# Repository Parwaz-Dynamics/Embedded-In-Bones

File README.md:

# Embedded-In-Bones 🦴

**My personal journey into embedded systems, from bare-metal programming to real-time operating systems.**

This repository documents my hands-on learning journey in embedded systems. It contains experiments, exercises, and projects as I work toward understanding what happens inside a microcontroller — from executing individual instructions to building real-time, event-driven applications.

## 🎯 Why This Repository?

I've worked with Arduino, ESP32, and Teensy platforms, along with STM32 microcontrollers such as the STM32F103, STM32F411, and STM32H723. Although I had some practical experience, I realized there was still a lot I wanted to understand at a deeper level.

Instead of relying entirely on frameworks and libraries, I decided to go back to the fundamentals: learning how processors execute instructions, how memory works, how interrupts are handled, and how embedded software can be designed to operate reliably in real time.

This repository is a record of that journey — including the concepts I've learned, the challenges I've faced, and the things I still need to explore.

## 📂 Learning Journey

### 1. Bare-Metal STM32F446

**Learning resource:** *Embedded Systems with ARM Cortex-M Microcontrollers in Assembly Language and C* by Dr. Yifeng Zhu.

I started by learning how to program a microcontroller close to the hardware, using ARM assembly language and C.

Topics covered include:

- ARM Cortex-M instruction set and processor registers
- Arithmetic, logical, shifting, and branching instructions
- Subroutines, structured programming, and mixing assembly with C
- Stack and heap fundamentals
- Static and volatile variables
- GPIO configuration and digital I/O
- Interrupts and timers
- Basic communication protocols
- Memory organization, including Flash and RAM
- Debugging and the software build process

This book helped me develop a clearer understanding of what happens inside a microcontroller when a program runs, rather than treating the hardware as a black box.

Along the way, I also gained practical experience with **Keil µVision**, ARM Compiler 6, and the GNU toolchain. I explored debugging, ELF files, linker scripts, and how code and data are organized in memory.

The final DSP chapter is still on my list to revisit.

📁 **Folder:** `Bare-Metal STM32F446/`

### 2. Real-Time Operating Systems — Quantum Leaps

**Learning resource:** [Quantum Leaps — YouTube lectures](https://www.youtube.com/@StateMachineCOM)

After completing most of the bare-metal material, I wanted to understand how embedded applications manage multiple concurrent activities and respond to events in real time.

I started following the Modern Embedded Systems programming lectures by Quantum Leaps. The early material reinforced some concepts I had already studied, but things became more challenging as the lectures progressed into interrupt handling, concurrency, and real-time operating systems.

During this stage, I worked through **MiROS**, a small real-time operating system, and then moved on to **QPC (QP/C)**.

Building and studying MiROS helped me explore concepts such as:

- Tasks and cooperative scheduling
- Preemptive scheduling and context switching
- Interrupt handling and synchronization
- Semaphores and blocking
- Communication and synchronization between concurrent tasks

My journey with QPC is ongoing. Next, I plan to explore state machines and event-driven programming to better understand how embedded applications can be structured without relying entirely on traditional blocking task-based designs.

📁 **Folder:** `Quantum Leap/`

## 🛠️ Tools & Technologies

- **Microcontrollers:** STM32F446 and other STM32 platforms
- **Programming languages:** C and ARM Assembly
- **IDE:** Keil µVision
- **Toolchains:** ARM Compiler 6 and GNU toolchain
- **Core topics:** Bare-metal programming, interrupts, timers, memory management, debugging, and RTOS fundamentals
- **RTOS / frameworks:** MiROS and QP/C

## 🚧 What's Next?

This journey is far from over.

This list will evolve as I learn and discover new areas worth exploring.

## 📌 A Note to Myself

Keep it up

------------------------------------------------

## 🔄 A Change in Direction: PCB Design & Embedded Systems Engineering

For now, I'm taking a slight detour from RTOS development to explore another important side of embedded systems: **PCB design and hardware development**.

I want to move beyond working with development boards and start understanding how to design and build my own PCBs. My plan is to learn the fundamentals of PCB design and manufacture one or two boards of my own.

Alongside this, I'll be reading *Making Embedded Systems* by **Elecia White**. I see this book as an opportunity to learn more about the broader engineering side of embedded systems, including how embedded projects are designed, developed, debugged, and managed.

My current plan is to:

- Learn the fundamentals of PCB design.
- Design and build one or two PCBs to gain practical experience.
- Read *Making Embedded Systems* by Elecia White.
- Return to Miro Samek's Modern Embedded Systems lectures after establishing a basic understanding of PCB design and completing my first boards.
- Meanwhile work on another project where I can practice the already learned techniques.

I'll resume the lectures from **Lecture #29 — Object-Oriented Programming**, where I paused.

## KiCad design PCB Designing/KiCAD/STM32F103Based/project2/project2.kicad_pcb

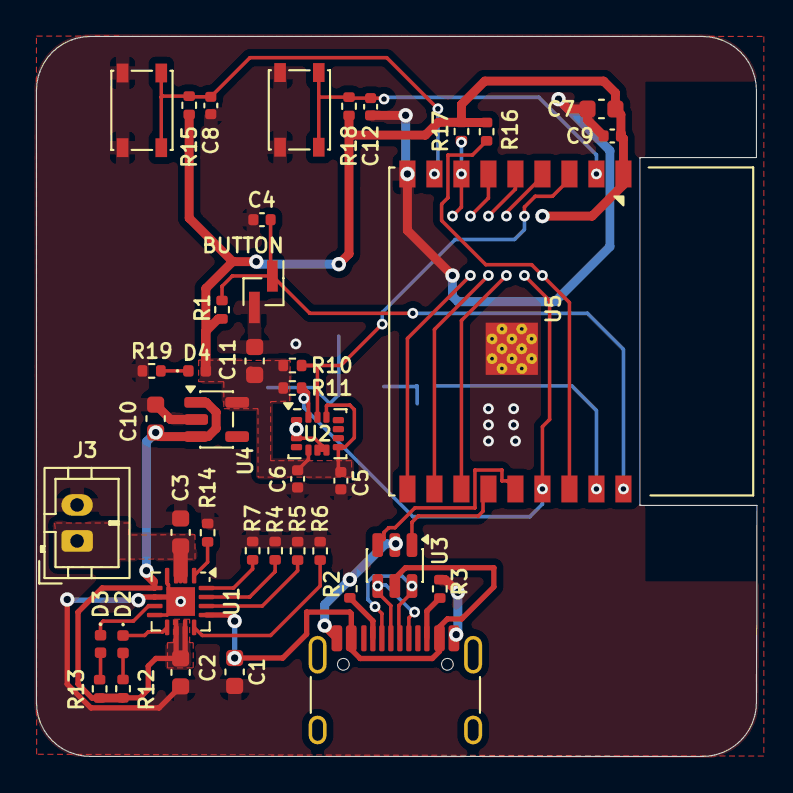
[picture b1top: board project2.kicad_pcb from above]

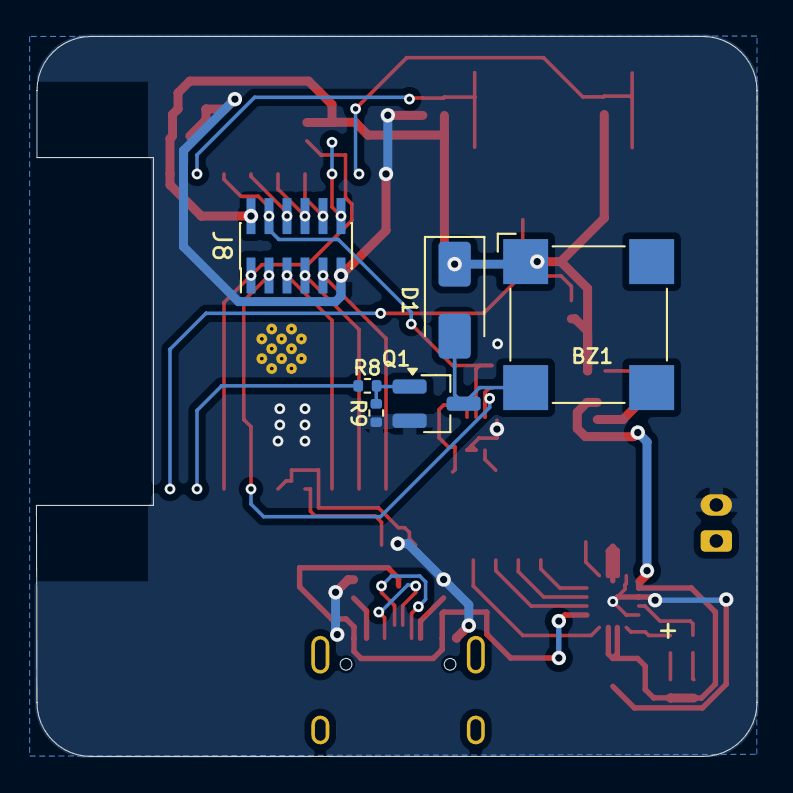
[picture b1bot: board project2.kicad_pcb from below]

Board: 2 copper layers, 40.0 x 40.0 mm, 48 parts (6 on the bottom side), 37 nets.

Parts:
BZ1: Buzzer; MagneticBuzzer_CUI_CMT-8504-100-SMT
C1, C10, C11: 1u; C_0603_1608Metric
C2, C3: 4u7; C_0603_1608Metric
C4, C5, C6, C8, C9, C12: 100n; C_0402_1005Metric
C7: 10u; C_0603_1608Metric
D1: SS14; D_SMA
D2, D3, D4: LED; LED_0402_1005Metric
J1: TYPE_C_31_M_12; USB_C_Receptacle_HRO_TYPE-C-31-M-12
J2: PLAY_BUTTON; PinHeader_1x02_P1.00mm_Vertical_SMD_Pin1Left
J3: BATT; JST_PH_B2B-PH-K_1x02_P2.00mm_Vertical
J8: Conn_02x06_Counter_Clockwise; PinHeader_2x06_P1.00mm_Vertical_SMD
Q1: AO3400A; SOT-23_Handsoldering
R1, R2, R3, R10, R11, R15, R18: 5k1; R_0402_1005Metric
R4: 4k7; R_0402_1005Metric
R5: 72k; R_0402_1005Metric
R6: 1k2; R_0402_1005Metric
R7: 3k3; R_0402_1005Metric
R8: 100; R_0402_1005Metric
R9, R14, R16, R17: 10k; R_0402_1005Metric
R12, R13, R19: 1k; R_0402_1005Metric
SW1: BOOT; SW_SPST_PTS810
SW2: NRST; SW_SPST_PTS810
U1: BQ24074RGT; VQFN-16-1EP_3x3mm_P0.5mm_EP1.6x1.6mm
U2: LSM6DS3TR-C; LGA-14_3x2.5mm_P0.5mm_LayoutBorder3x4y
U3: USBLC6-2SC6; SOT-23-6
U4: AP2112K-3.3; SOT-23-5
U5: ESP32-C3-WROOM-02

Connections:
+3.3V: BZ1.1 (+), C5.2, C6.2, C7.1, C9.1, C11.1, D1.1 (K), D4.2 (A), J8.2, R1.2, R10.2, R11.2, R15.2, R16.2, R17.2, R18.2, U2.5 (VDDIO), U2.8 (VDD), U2.12 (CS), U4.5 (VOUT), U5.1 (3V3)
+BATT: C3.1, J3.1, U1.2 (BAT), U1.3 (BAT)
/BOOT: C8.1, R15.1, SW1.2, U5.8 (IO9)
/BUZZER_MCU: R8.2, U5.17 (IO1)
/CHIP_EN: C12.1, R18.1, SW2.2, U5.2 (EN)
/I2C_SCL: J8.4, R10.1, U2.13 (SCL), U5.3 (IO4)
/I2C_SDA: J8.3, R11.1, U2.14 (SDA), U5.15 (IO3)
/IO2: J8.1, R16.1, U5.16 (IO2)
/IO5: J8.6, U5.4 (IO5)
/IO6: J8.8, U5.5 (IO6)
/IO7: J8.10, U5.6 (IO7)
/IO8: J8.12, R17.1, U5.7 (IO8)
/IO10: J8.9, U5.10 (IO10)
/MCU_USB_D_N: U3.1 (I/O1), U5.13 (IO18)
/MCU_USB_D_P: U3.3 (I/O2), U5.14 (IO19)
/PLAY_BUTTON_MCU: C4.1, J2.1, R1.1, U5.18 (IO0)
/PWR_LED_K: D4.1 (K), R19.1
/RXD: J8.7, U5.11 (IO20/RXD)
/TXD: J8.5, U5.12 (IO21/TXD)
/USB_D_N: J1.A7 (D-), J1.B7 (D-), U3.6 (I/O1)
/USB_D_P: J1.A6 (D+), J1.B6 (D+), U3.4 (I/O2)
GND: C1.2, C2.2, C3.2, C4.2, C5.1, C6.1, C7.2, C8.2, C9.2, C10.2, C11.2, C12.2, J1.A1 (GND), J1.A12 (GND), J1.B1 (GND), J1.B12 (GND), J2.2, J3.2, J8.11, Q1.2 (S), R2.2, R3.2, R4.1, R5.1, R6.1, R7.1, R9.2, R14.2, R19.2, SW1.1, SW2.1, U1.4 (~CE), U1.6 (EN1), U1.8 (VSS), U1.17 (VSS), U2.1 (SDO/SA0), U2.2 (SDX), U2.3 (SCX), U2.6 (GND), U2.7 (GND), U3.2 (GND), U4.2 (GND), U5.9 (GND), U5.19 (GND)
unnamed: BZ1.2 (-), D1.2 (A), Q1.3 (D)
unnamed: D2.2 (A), R12.1
unnamed: D2.1 (K), U1.9 (~CHG)
unnamed: D3.2 (A), R13.1
unnamed: D3.1 (K), U1.7 (~PGOOD)
unnamed: J1.A5 (CC1), R2.1
unnamed: J1.B5 (CC2), R3.1
unnamed: Q1.1 (G), R8.1, R9.1
unnamed: R6.2, U1.12 (ILIM)
unnamed: R7.2, U1.16 (ISET)
unnamed: R4.2, U1.15 (ITERM)
unnamed: R5.2, U1.14 (TMR)
unnamed: R14.1, U1.1 (TS)
VBUS: C1.1, J1.A4 (VBUS), J1.A9 (VBUS), J1.B4 (VBUS), J1.B9 (VBUS), U1.13 (IN), U3.5 (VBUS)
VSYS: C2.1, C10.1, R12.2, R13.2, U1.5 (EN2), U1.10 (OUT), U1.11 (OUT), U4.1 (VIN), U4.3 (EN)

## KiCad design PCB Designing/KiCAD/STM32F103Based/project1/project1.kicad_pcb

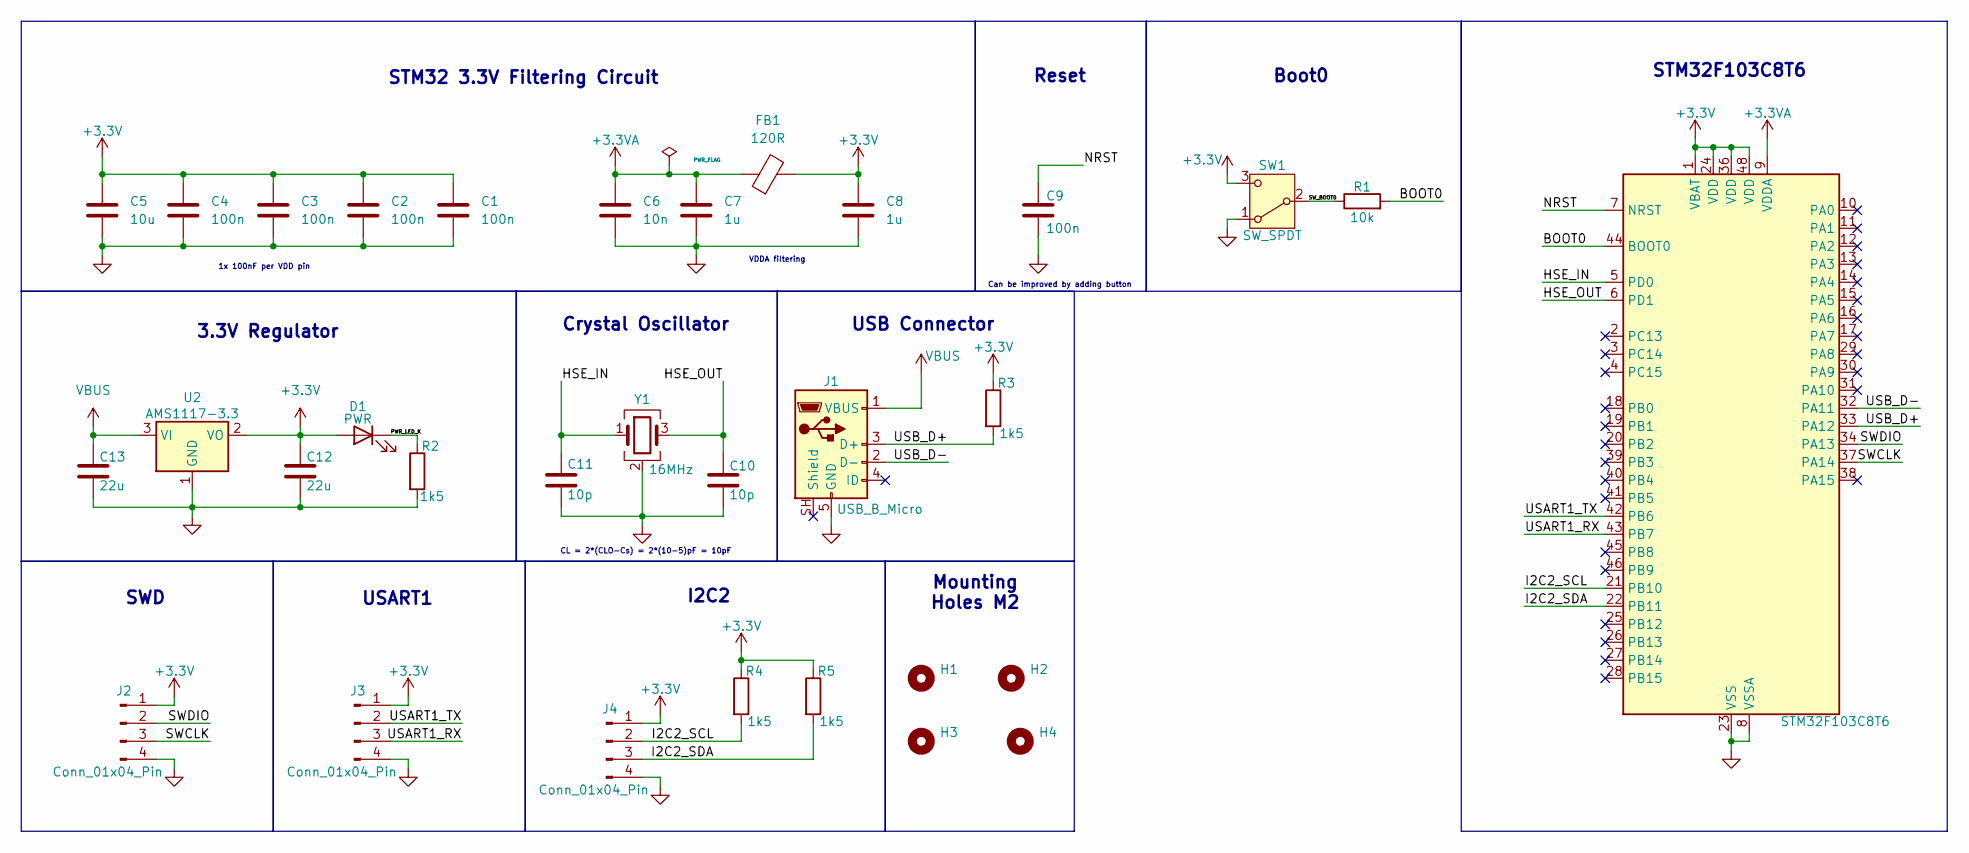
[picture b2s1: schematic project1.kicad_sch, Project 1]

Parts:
C1, C2, C3, C4, C9: 100n; C_0402_1005Metric
C5: 10u; C_0603_1608Metric
C6: 10n; C_0402_1005Metric
C7, C8: 1u; C_0402_1005Metric
C10, C11: 10p; C_0402_1005Metric
C12, C13: 22u; C_0805_2012Metric
D1: PWR; LED_0603_1608Metric
FB1: 120R; L_0603_1608Metric
H1, H2, H3, H4: MountingHole; MountingHole_2.2mm_M2
J1: USB_B_Micro; USB_Micro-B_Wuerth_629105150521
J2, J3, J4: Conn_01x04_Pin; PinHeader_1x04_P2.54mm_Vertical
R1: 10k; R_0402_1005Metric
R2, R3, R4, R5: 1k5; R_0402_1005Metric
SW1: SW_SPDT; SW_SPDT_PCM12
U1: STM32F103C8T6; LQFP-48_7x7mm_P0.5mm
U2: AMS1117-3.3; SOT-223-3_TabPin2
Y1: 16MHz; Crystal_SMD_3225-4Pin_3.2x2.5mm

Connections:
+3.3V: C1.1, C2.1, C3.1, C4.1, C5.1, C8.1, C12.1, D1.2 (A), FB1.2, J2.1, J3.1, J4.1, R3.1, R4.1, R5.1, SW1.3 (C), U1.1 (VBAT), U1.24 (VDD), U1.36 (VDD), U1.48 (VDD), U2.2 (VO)
+3.3VA: C6.1, C7.1, FB1.1, U1.9 (VDDA)
/BOOT0: R1.2, U1.44 (BOOT0)
/HSE_IN: C11.1, U1.5 (PD0), Y1.1
/HSE_OUT: C10.1, U1.6 (PD1), Y1.3
/I2C2_SCL: J4.2, R4.2, U1.21 (PB10)
/I2C2_SDA: J4.3, R5.2, U1.22 (PB11)
/NRST: C9.1, U1.7 (NRST)
/PWR_LED_K: D1.1 (K), R2.1
/SWCLK: J2.3, U1.37 (PA14)
/SWDIO: J2.2, U1.34 (PA13)
/SW_BOOT0: R1.1, SW1.2 (B)
/USART1_RX: J3.3, U1.43 (PB7)
/USART1_TX: J3.2, U1.42 (PB6)
/USB_D+: J1.3 (D+), R3.2, U1.33 (PA12)
/USB_D-: J1.2 (D-), U1.32 (PA11)
GND: C1.2, C2.2, C3.2, C4.2, C5.2, C6.2, C7.2, C8.2, C9.2, C10.2, C11.2, C12.2, C13.2, J1.5 (GND), J2.4, J3.4, J4.4, R2.2, SW1.1 (A), U1.8 (VSSA), U1.23 (VSS), U1.35 (VSS), U1.47 (VSS), U2.1 (GND), Y1.2 (G), Y1.4 (G)
VBUS: C13.1, J1.1 (VBUS), U2.3 (VI)

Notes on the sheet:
1x 100nF per VDD pin
I2C2
VDDA filtering
Boot0
Mounting Holes M2
3.3V Regulator
Crystal Oscillator
USB Connector
STM32 3.3V Filtering Circuit
USART1
SWD
CL = 2*(CLO-Cs) = 2*(10-5)pF = 10pF
STM32F103C8T6
Can be improved by adding button
Reset

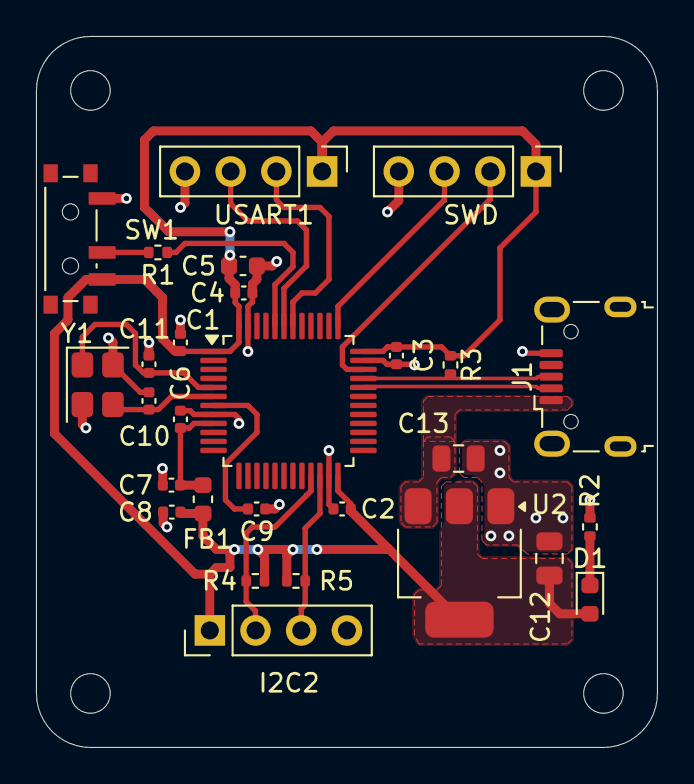
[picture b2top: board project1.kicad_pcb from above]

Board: 2 copper layers, 34.5 x 39.5 mm, 32 parts (0 on the bottom side), 18 nets.
